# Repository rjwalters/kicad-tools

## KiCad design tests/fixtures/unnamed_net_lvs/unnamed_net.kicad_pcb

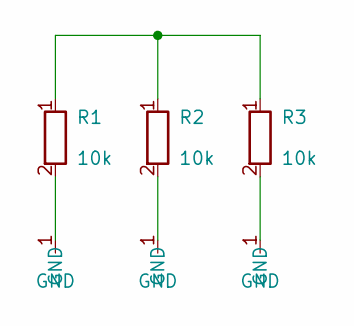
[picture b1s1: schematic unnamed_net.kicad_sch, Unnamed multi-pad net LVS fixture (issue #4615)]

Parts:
R1, R2, R3: 10k; R_0402_1005Metric

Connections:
GND: R1.2, R2.2, R3.2
unnamed: R1.1, R2.1, R3.1

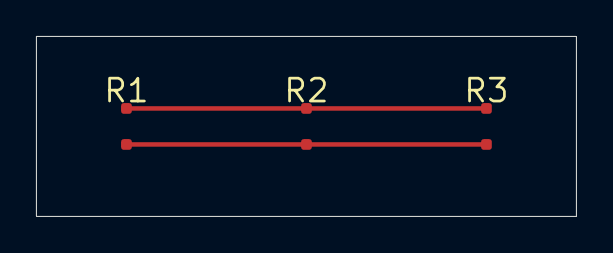
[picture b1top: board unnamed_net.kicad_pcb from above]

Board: 2 copper layers, 30.0 x 10.0 mm, 3 parts (0 on the bottom side), 2 nets.
